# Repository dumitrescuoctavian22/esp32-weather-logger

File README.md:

# esp32-weather-logger
An ESP32 weather logger, covering temperature, humidity, air quality, and real time clock, saving to a micro SD card.

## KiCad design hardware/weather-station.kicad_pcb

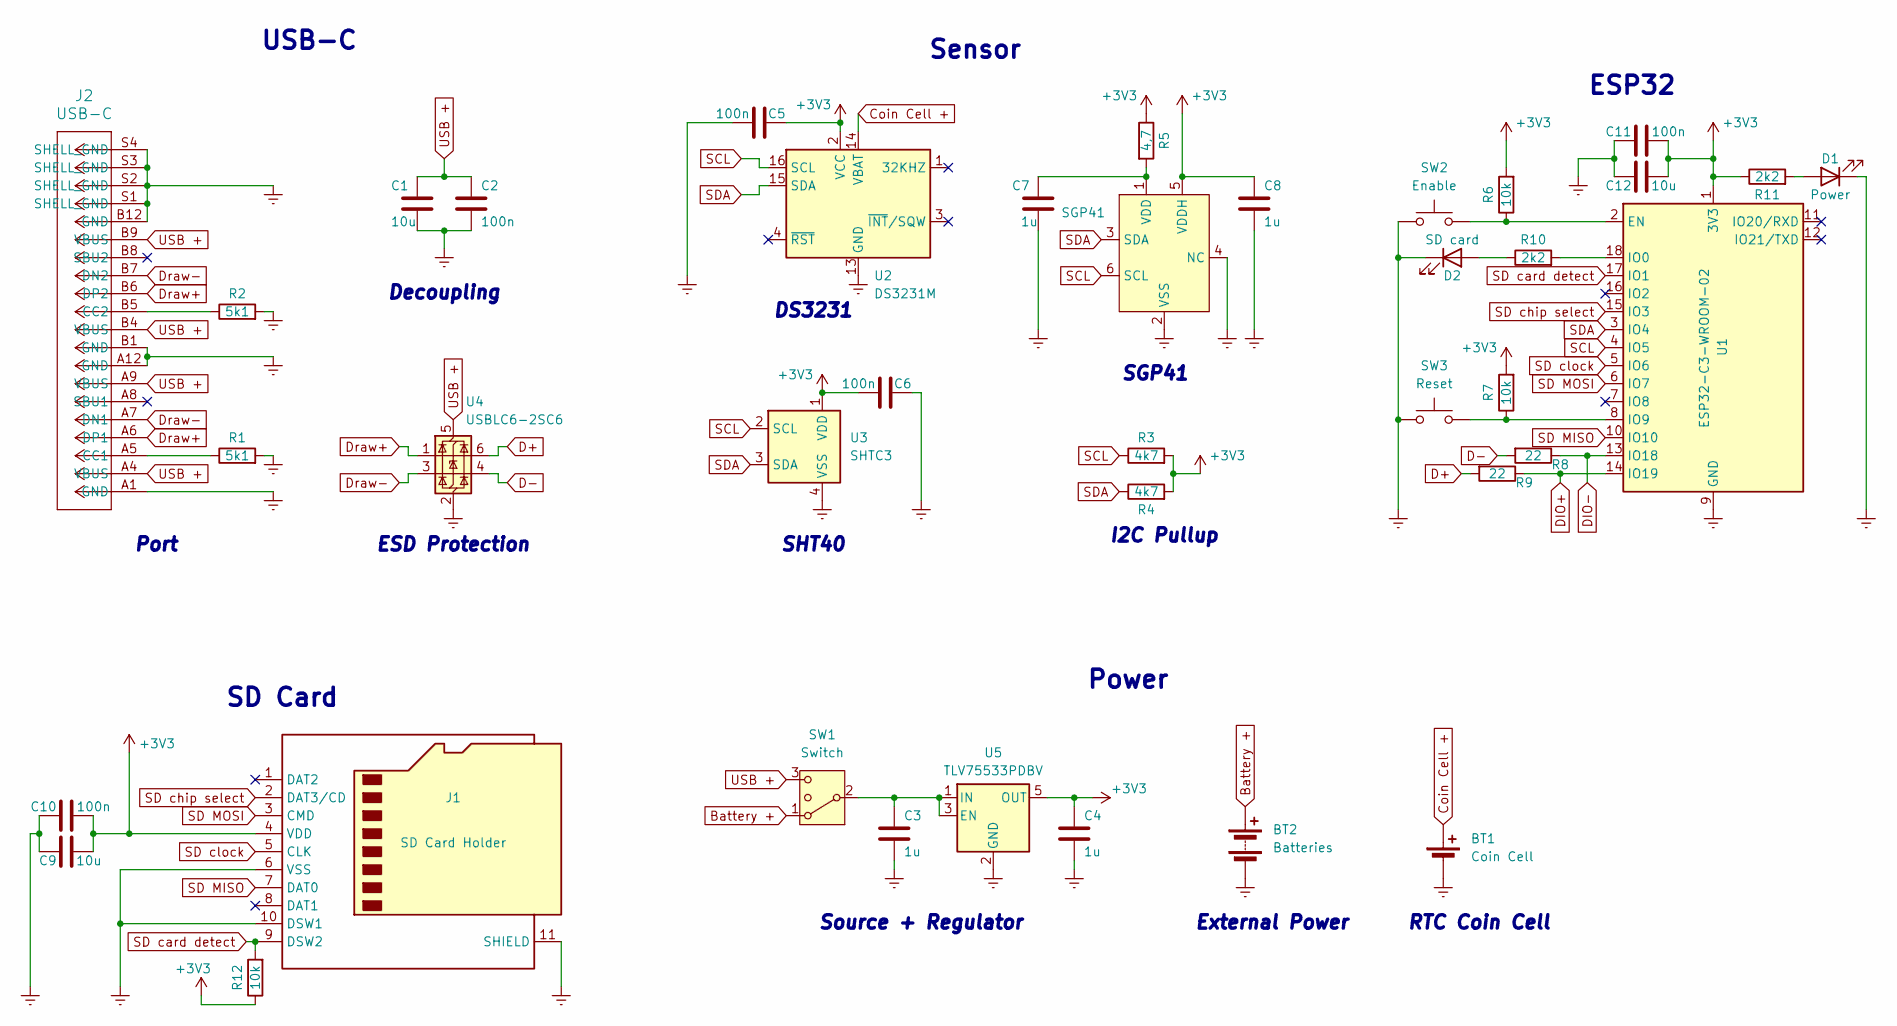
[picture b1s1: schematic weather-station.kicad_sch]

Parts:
BT1: Coin Cell
BT2: Batteries; TerminalBlock_Phoenix_MPT-0,5-2-2.54_1x02_P2.54mm_Horizontal
C1, C9, C12: 10u; C_0805_2012Metric_Pad1.18x1.45mm_HandSolder
C2, C5, C6, C10, C11: 100n; C_0805_2012Metric_Pad1.18x1.45mm_HandSolder
C3, C4, C7, C8: 1u; C_0805_2012Metric_Pad1.18x1.45mm_HandSolder
D1: Power; LED_0805_2012Metric_Pad1.15x1.40mm_HandSolder
D2: SD card; LED_0805_2012Metric_Pad1.15x1.40mm_HandSolder
J1: SD Card Holder; SD card receptable
J2: USB-C; CONN16_C16PIN_SHN
R1, R2: 5k1; R_0805_2012Metric_Pad1.20x1.40mm_HandSolder
R3, R4: 4k7; R_0805_2012Metric_Pad1.20x1.40mm_HandSolder
R5: 4,7; R_0805_2012Metric_Pad1.20x1.40mm_HandSolder
R6, R7, R12: 10k; R_0805_2012Metric_Pad1.20x1.40mm_HandSolder
R8, R9: 22; R_0805_2012Metric_Pad1.20x1.40mm_HandSolder
R10, R11: 2k2; R_0805_2012Metric_Pad1.20x1.40mm_HandSolder
SGP41: SGP41
SW1: Switch; ON-OFF-ON Switch
SW2: Enable; SW_PUSH_6mm_H5mm
SW3: Reset; SW_PUSH_6mm_H5mm
U1: ESP32-C3-WROOM-02
U2: DS3231M; SOIC-16W_7.5x10.3mm_P1.27mm
U3: SHTC3; Sensirion_DFN-4-1EP_2x2mm_P1mm_EP0.7x1.6mm
U4: USBLC6-2SC6; SOT-23-6
U5: TLV75533PDBV; SOT-23-5

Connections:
+3V3: C4.1, C5.2, C6.1, C8.1, C9.2, C10.2, C11.2, C12.2, J1.4 (VDD), R3.2, R4.2, R5.1, R6.2, R7.2, R11.1, R12.1, SGP41.5 (VDDH), U1.1 (3V3), U2.2 (VCC), U3.1 (VDD), U5.5 (OUT)
Battery +: BT2.1 (+), SW1.1
Coin Cell +: BT1.1 (+), U2.14 (VBAT)
D+: R9.2, U4.6 (I/O1)
D-: R8.2, U4.4 (I/O2)
DIO+: R9.1, U1.14 (IO19)
DIO-: R8.1, U1.13 (IO18)
Draw+: J2.A6 (DP1), J2.B6 (DP2), U4.1 (I/O1)
Draw-: J2.A7 (DN1), J2.B7 (DN2), U4.3 (I/O2)
Earth: BT1.2 (-), BT2.2 (-), C1.2, C2.2, C3.2, C4.2, C5.1, C6.2, C7.2, C8.2, C9.1, C10.1, C11.1, C12.1, D1.1 (K), D2.1 (K), J1.6 (VSS), J1.10 (DSW1), J1.11 (SHIELD), J2.A1 (GND), J2.A12 (GND), J2.B1 (GND), J2.B12 (GND), J2.S1 (SHELL_GND), J2.S2 (SHELL_GND), J2.S3 (SHELL_GND), J2.S4 (SHELL_GND), R1.2, R2.2, SGP41.2 (VSS), SGP41.4 (NC), SW2.1, SW3.1, U1.9 (GND), U1.19 (GND), U2.5 (GND), U2.6 (GND), U2.7 (GND), U2.8 (GND), U2.9 (GND), U2.10 (GND), U2.11 (GND), U2.12 (GND), U2.13 (GND), U3.4 (VSS), U4.2 (GND), U5.2 (GND)
unnamed: D1.2 (A), R11.2
unnamed: D2.2 (A), R10.1
unnamed: J2.A5 (CC1), R1.1
unnamed: J2.B5 (CC2), R2.1
unnamed: C7.1, R5.2, SGP41.1 (VDD)
unnamed: C3.1, SW1.2 (3), U5.1 (IN), U5.3 (EN)
unnamed: R6.1, SW2.2, U1.2 (EN)
unnamed: R10.2, U1.18 (IO0)
unnamed: R7.1, SW3.2, U1.8 (IO9)
SCL: R3.1, SGP41.6 (SCL), U1.4 (IO5), U2.16 (SCL), U3.2 (SCL)
SD MISO: J1.7 (DAT0), U1.10 (IO10)
SD MOSI: J1.3 (CMD), U1.6 (IO7)
SD card detect: J1.9 (DSW2), R12.2, U1.17 (IO1)
SD chip select: J1.2 (DAT3/CD), U1.15 (IO3)
SD clock: J1.5 (CLK), U1.5 (IO6)
SDA: R4.1, SGP41.3 (SDA), U1.3 (IO4), U2.15 (SDA), U3.3 (SDA)
USB +: C1.1, C2.1, J2.A4 (VBUS), J2.A9 (VBUS), J2.B4 (VBUS), J2.B9 (VBUS), SW1.3 (4), U4.5 (VBUS)

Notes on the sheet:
Power
Port
Decoupling
ESD Protection
I2C Pullup
External Power
DS3231
RTC Coin Cell
SGP41
Source + Regulator
Sensor
SHT40
SD Card
ESP32
USB-C

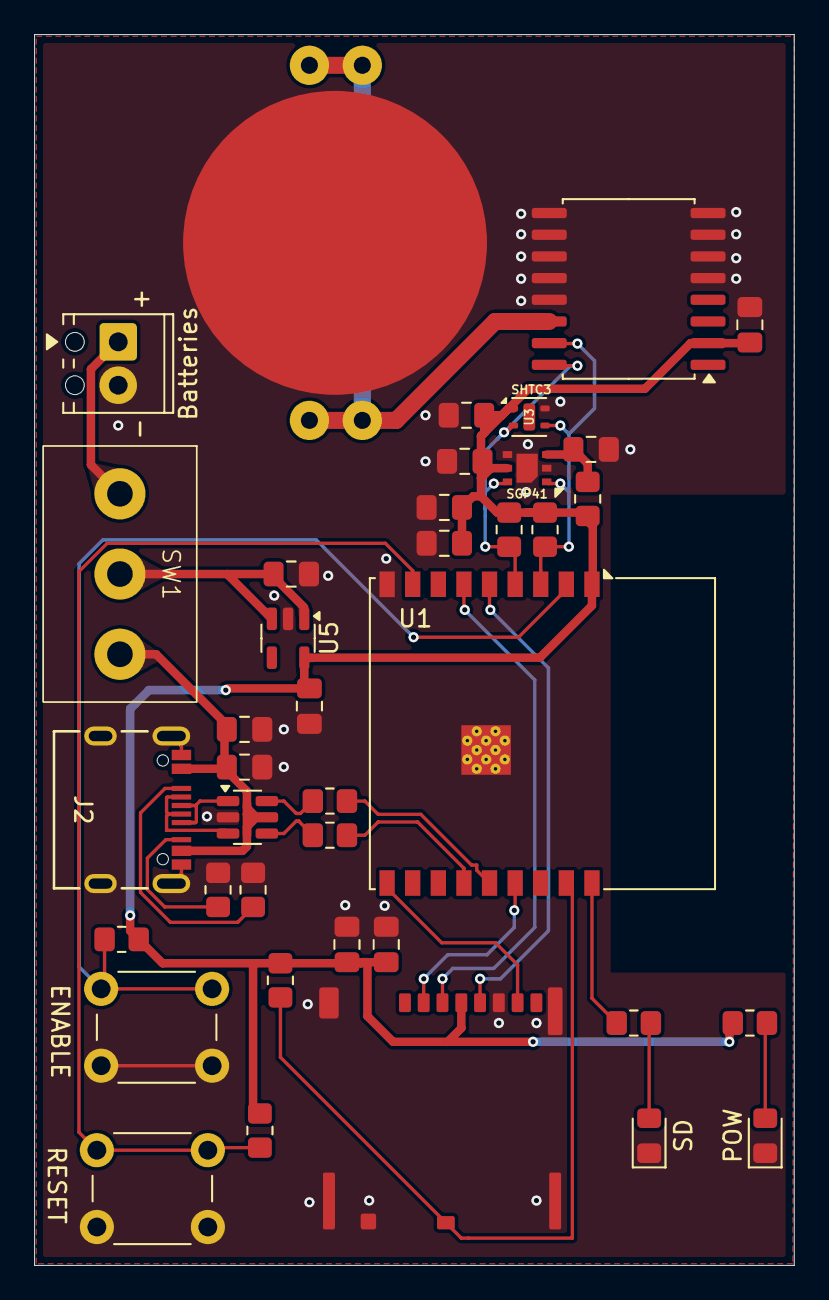
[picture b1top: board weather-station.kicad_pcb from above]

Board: 2 copper layers, 44.5 x 72.1 mm, 39 parts (0 on the bottom side), 27 nets.
